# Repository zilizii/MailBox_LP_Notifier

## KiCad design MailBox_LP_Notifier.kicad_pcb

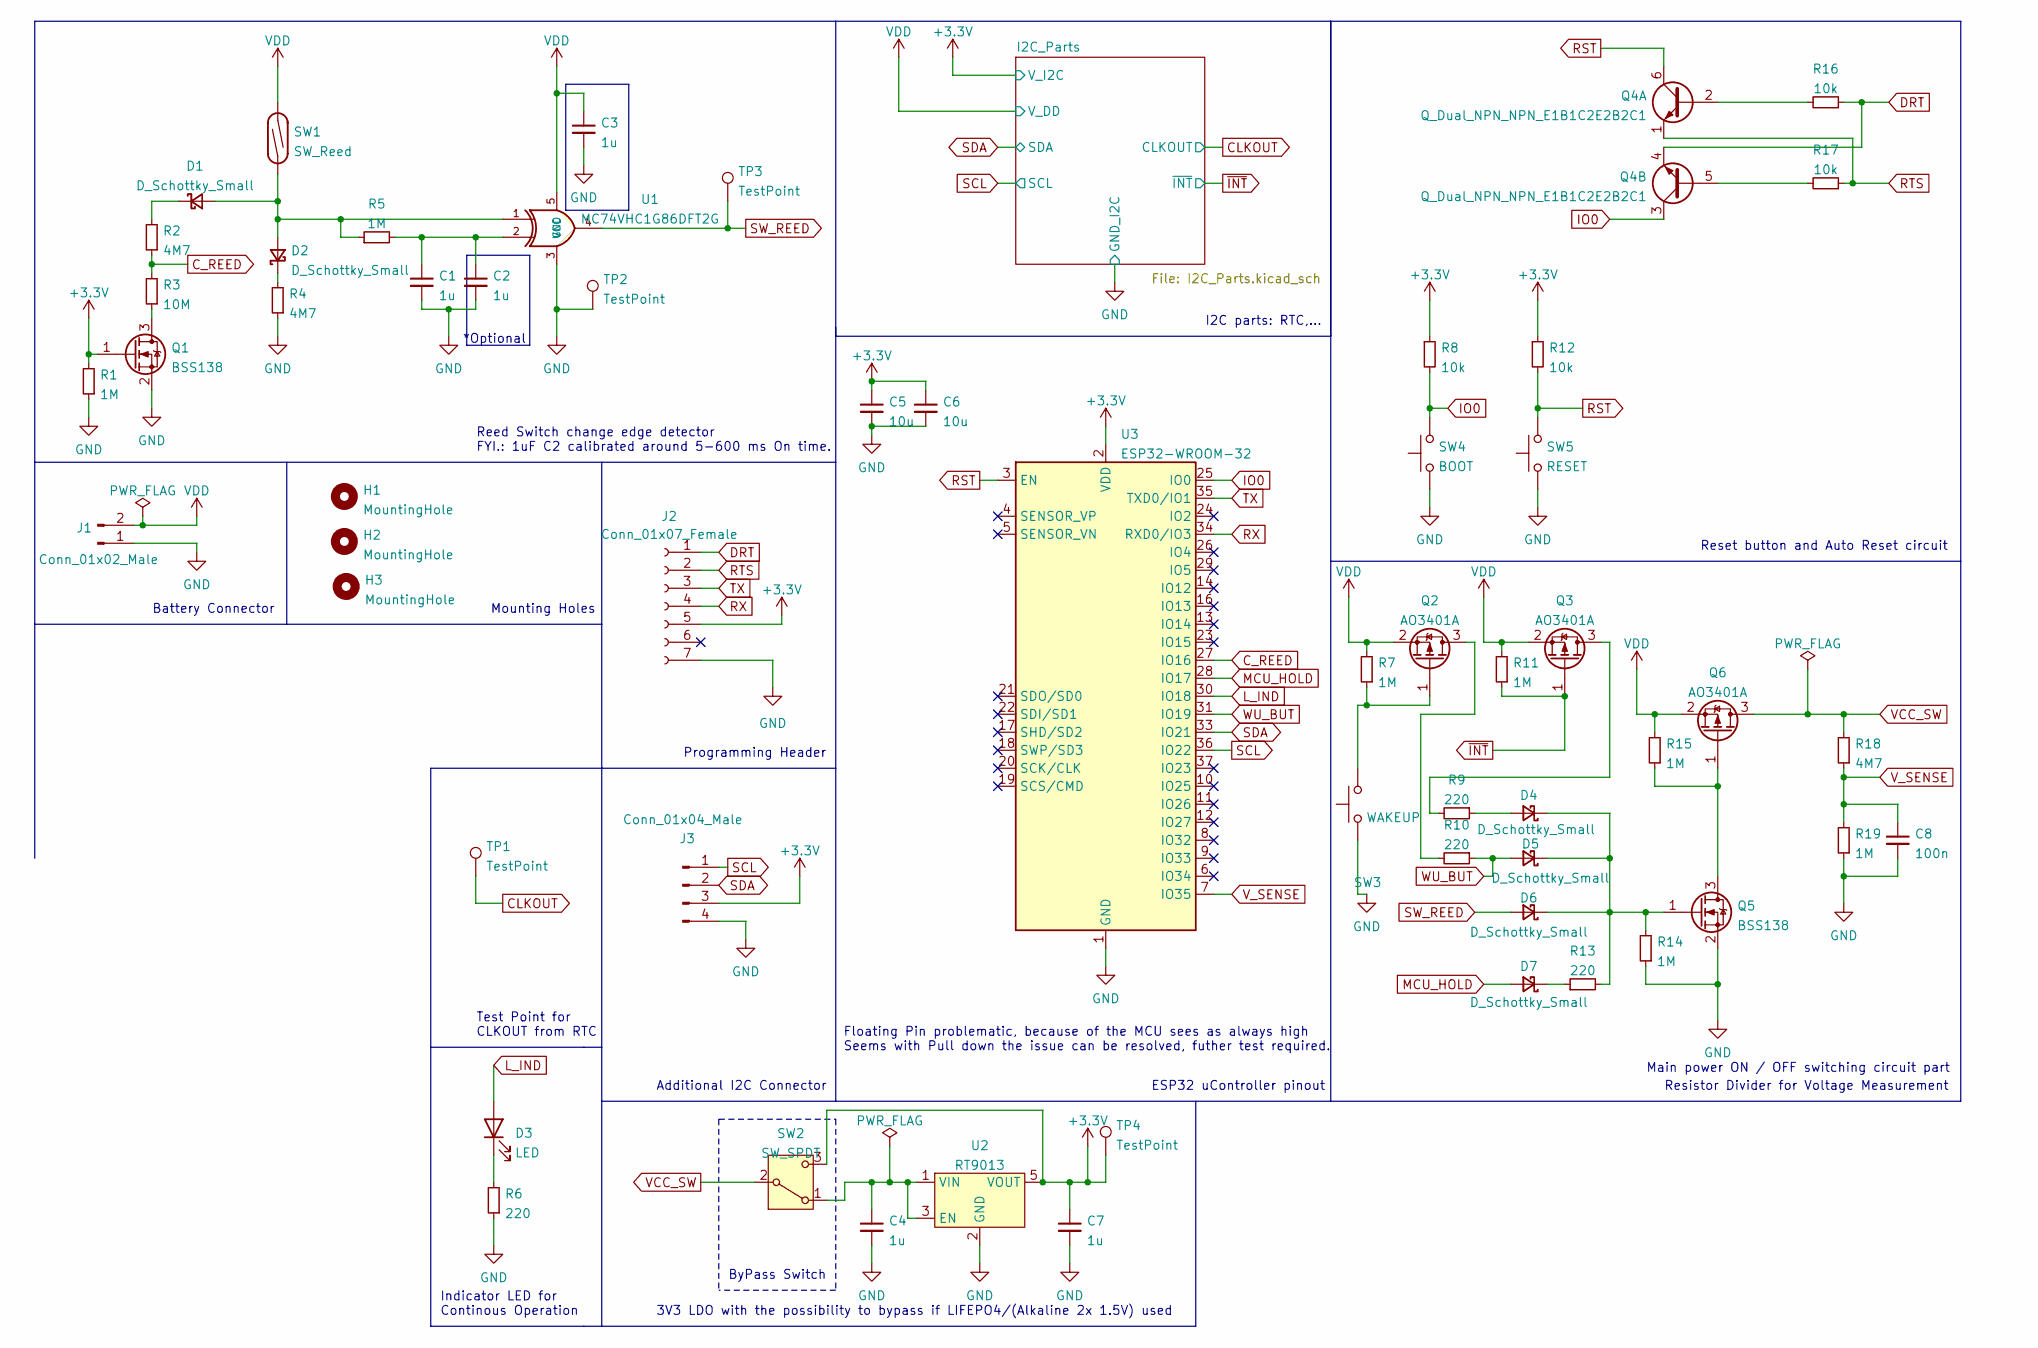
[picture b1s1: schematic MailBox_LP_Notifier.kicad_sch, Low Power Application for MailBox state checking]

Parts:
C1, C2, C3, C4, C7: 1u; C_0603_1608Metric
C5, C6: 10u; C_0603_1608Metric
C8: 100n; C_0603_1608Metric
D1, D2, D4, D5, D6, D7: D_Schottky_Small; D_SOD-123
D3: LED; LED_0805_2012Metric
H1, H2, H3: MountingHole; MountingHole_3.2mm_M3_DIN965
J1: Conn_01x02_Male; JST_PH_B2B-PH-K_1x02_P2.00mm_Vertical
J2: Conn_01x07_Female; PinSocket_1x07_P2.54mm_Vertical
J3: Conn_01x04_Male; JST_PH_S4B-PH-K_1x04_P2.00mm_Horizontal
Q1, Q5: BSS138; SOT-23
Q2, Q3, Q6: AO3401A; SOT-23
Q4: Q_Dual_NPN_NPN_E1B1C2E2B2C1; SOT-363_SC-70-6
R1, R5, R7, R11, R14, R15, R19: 1M; R_0603_1608Metric
R2, R4, R18: 4M7; R_0603_1608Metric
R3: 10M; R_0603_1608Metric
R6, R13: 220; R_0805_2012Metric
R8, R12, R16, R17: 10k; R_0603_1608Metric
R9, R10: 220; R_0603_1608Metric
SW1: SW_Reed; Molex_Micro-Fit_3.0_43045-0200_2x01_P3.00mm_Horizontal
SW2: SW_SPDT; SW_SPDT_PCM12
SW3: WAKEUP; SW_SPST_CK_RS282G05A3
SW4: BOOT; SW_SPST_CK_RS282G05A3
SW5: RESET; SW_SPST_CK_RS282G05A3
TP1, TP2, TP3, TP4: TestPoint; TestPoint_Pad_D1.0mm
U1: MC74VHC1G86DFT2G; SOT-23-5
U2: RT9013; SOT-23-5
U3: ESP32-WROOM-32

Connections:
+3.3V: C5.1, C6.1, C7.1, J2.5, J3.3, Q1.1 (G), R1.2, R8.1, R12.1, SW2.3 (C), TP4.1, U2.5 (VOUT), U3.2 (VDD); also elsewhere on the board
CLKOUT: TP1.1; also elsewhere on the board
C_REED: R2.1, R3.2, U3.27 (IO16)
DRT: J2.1, Q4.4 (E2), R16.1
GND: C1.2, C2.2, C3.2, C4.2, C5.2, C6.2, C7.2, C8.2, J1.1, J2.7, J3.4, Q1.2 (S), Q5.2 (S), R1.1, R4.1, R6.1, R14.1, R19.1, SW3.1, SW4.1, SW5.1, TP2.1, U1.3 (GND), U2.2 (GND), U3.1 (GND), U3.15 (GND), U3.38 (GND), U3.39 (GND); also elsewhere on the board
IO0: Q4.3 (C2), R8.2, SW4.2, U3.25 (IO0)
L_IND: D3.2 (A), U3.30 (IO18)
MCU_HOLD: D7.2 (A), U3.28 (IO17)
unnamed: C1.1, C2.1, R5.2, U1.2
unnamed: D1.2 (A), D2.2 (A), R5.1, SW1.1, U1.1
unnamed: D1.1 (K), R2.2
unnamed: D2.1 (K), R4.2
unnamed: D3.1 (K), R6.2
unnamed: D4.2 (A), R9.1
unnamed: D4.1 (K), D5.1 (K), D6.1 (K), Q5.1 (G), R13.2, R14.2
unnamed: D7.1 (K), R13.1
unnamed: Q1.3 (D), R3.1
unnamed: Q2.3 (D), R10.2
unnamed: Q2.1 (G), R7.1, SW3.2
unnamed: Q3.3 (D), R9.2
unnamed: Q4.2 (B1), R16.2
unnamed: Q4.5 (B2), R17.2
unnamed: Q5.3 (D), Q6.1 (G), R15.1
unnamed: C4.1, SW2.1 (A), U2.1 (VIN), U2.3 (EN)
RST: Q4.6 (C1), R12.2, SW5.2, U3.3 (EN)
RTS: J2.2, Q4.1 (E1), R17.1
RX: J2.4, U3.34 (RXD0/IO3)
SCL: J3.1, U3.36 (IO22); also elsewhere on the board
SDA: J3.2, U3.33 (IO21); also elsewhere on the board
SW_REED: D6.2 (A), TP3.1, U1.4
TX: J2.3, U3.35 (TXD0/IO1)
VCC_SW: Q6.3 (D), R18.2, SW2.2 (B)
VDD: C3.1, J1.2, Q2.2 (S), Q3.2 (S), Q6.2 (S), R7.2, R11.2, R15.2, SW1.2, U1.5 (VCC); also elsewhere on the board
V_SENSE: C8.1, R18.1, R19.2, U3.7 (IO35)
WU_BUT: D5.2 (A), R10.1, U3.31 (IO19)
~INT: Q3.1 (G), R11.1; also elsewhere on the board

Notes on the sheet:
Reset button and Auto Reset circuit
Mounting Holes
ESP32 uController pinout
ByPass Switch
Battery Connector
*Optional
I2C parts: RTC,...
Programming Header
Main power ON / OFF switching circuit part
Resistor Divider for Voltage Measurement
Test Point for CLKOUT from RTC
Indicator LED for Continous Operation
3V3 LDO with the possibility to bypass if LIFEPO4/(Alkaline 2x 1.5V) used
Reed Switch change edge detector FYI.: 1uF C2 calibrated around 5-600 ms On time.
Floating Pin problematic, because of the MCU sees as always high Seems with Pull down the issue can be resolved, futher test required.
Additional I2C Connector

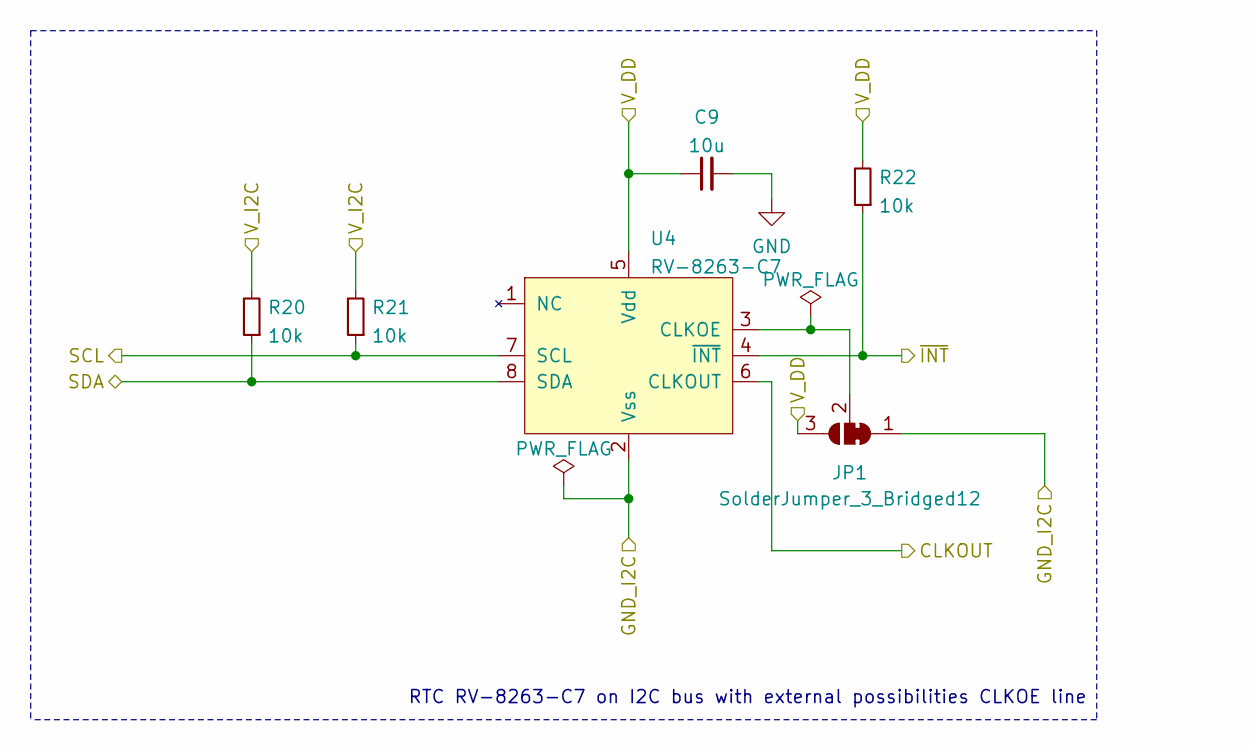
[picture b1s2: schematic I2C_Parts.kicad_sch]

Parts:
C9: 10u; C_0603_1608Metric
JP1: SolderJumper_3_Bridged12; SolderJumper-3_P1.3mm_Bridged2Bar12_RoundedPad1.0x1.5mm
R20, R21, R22: 10k; R_0603_1608Metric
U4: RV-8263-C7; C7

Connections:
+3.3V: R20.2, R21.2; also elsewhere on the board
CLKOUT: U4.6 (CLKOUT); also elsewhere on the board
GND: C9.2, JP1.1 (A), U4.2 (Vss); also elsewhere on the board
unnamed: JP1.2 (C), U4.3 (CLKOE)
SCL: R21.1, U4.7 (SCL); also elsewhere on the board
SDA: R20.1, U4.8 (SDA); also elsewhere on the board
VDD: C9.1, JP1.3 (B), R22.2, U4.5 (Vdd); also elsewhere on the board
~INT: R22.1, U4.4 (~INT); also elsewhere on the board

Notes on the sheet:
RTC RV-8263-C7 on I2C bus with external possibilities CLKOE line

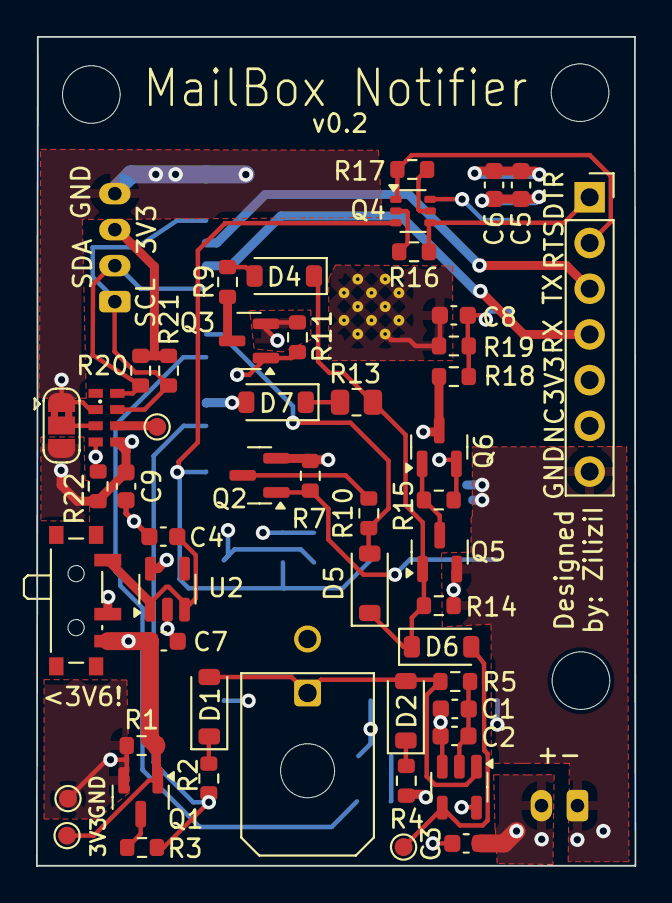
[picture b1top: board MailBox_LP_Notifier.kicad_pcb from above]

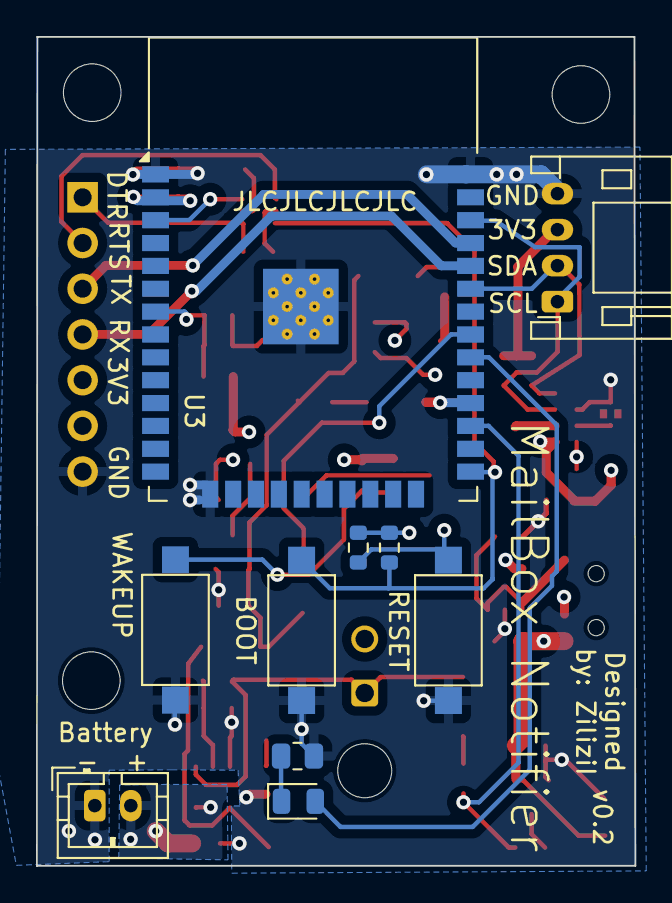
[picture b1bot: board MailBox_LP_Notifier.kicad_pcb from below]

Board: 4 copper layers, 33.2 x 46.1 mm, 64 parts (10 on the bottom side), 37 nets.

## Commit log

2024-06-27 Project MailBox Notifier init
